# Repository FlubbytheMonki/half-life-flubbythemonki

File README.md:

I recently started working on starbie, a physical, sort of tomogotchi thats a star. It responds to your actions with controls on the board itself, designed in Kicad. 
This is really cool. Theres a menu that you can control with the buttons on the side and everything lays on the design that we made in Kicad. 
I feel like KiCad opened a whole new aspect of embedded programming that I never knew about. I thought pcbs were really hard to do but turns out that that isnt entirely the case.

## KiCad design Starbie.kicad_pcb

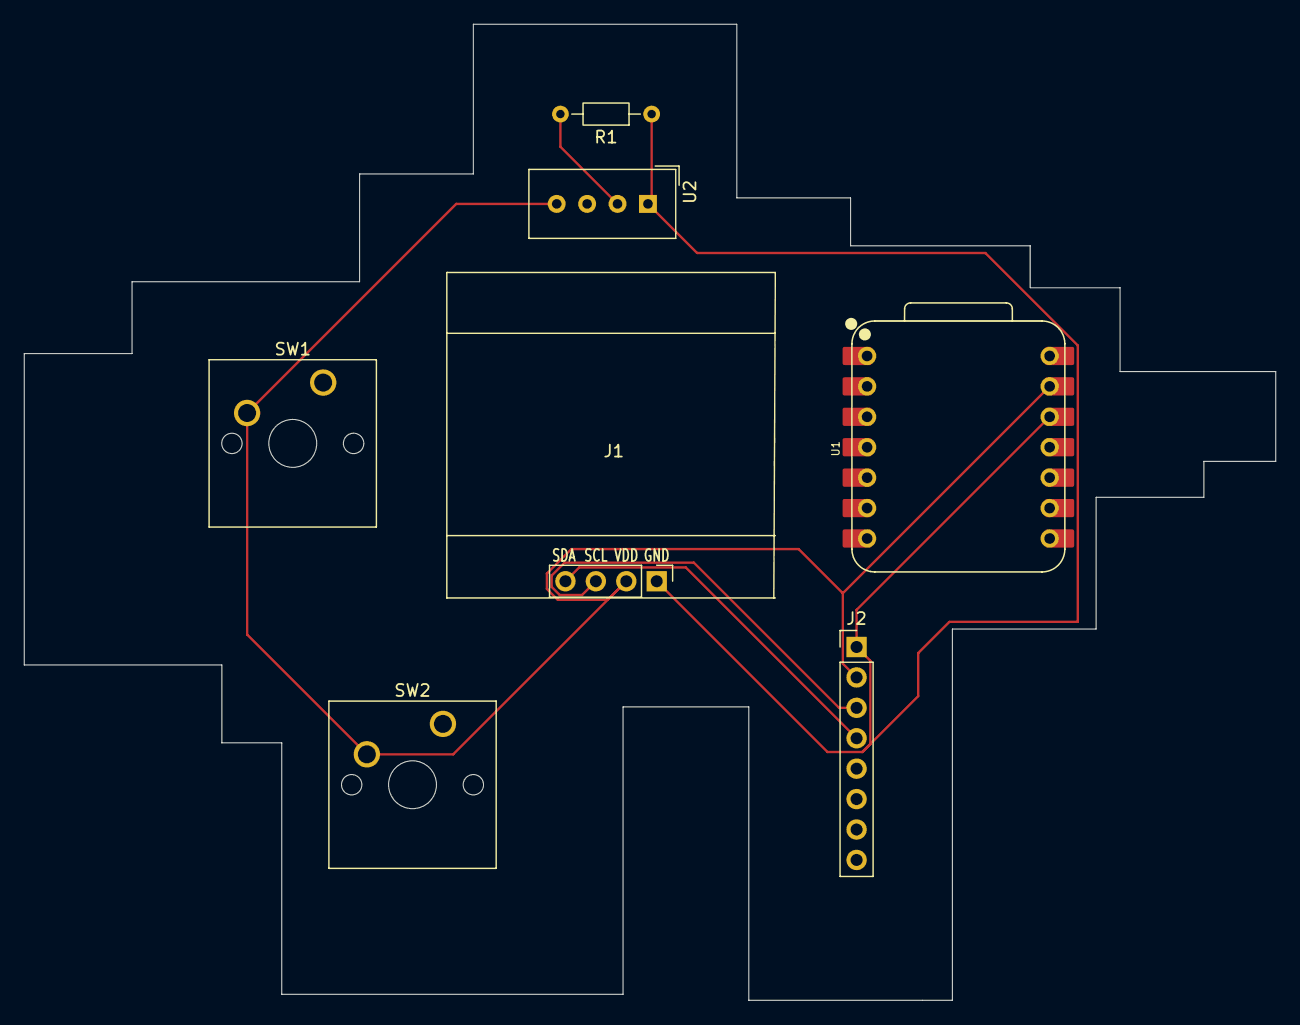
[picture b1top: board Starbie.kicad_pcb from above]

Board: 2 copper layers, 104.5 x 81.5 mm, 7 parts (0 on the bottom side), 5 nets.

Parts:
J1: Conn_01x04_Pin; Display_128x64_096_I2C
J2: Conn_01x08_Pin; PinHeader_1x08_P2.54mm_Vertical
R1: 10k; R_Axial_DIN0204_L3.6mm_D1.6mm_P7.62mm_Horizontal
SW1, SW2: SW_Push; SW_Cherry_MX_1.00u_PCB
U1: XIAO-ESP32-C3-SMD; XIAO-ESP32-C6-DIP
U2: DHT11; Aosong_DHT11_5.5x12.0_P2.54mm

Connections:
+3.3V: J1.1, J2.1, R1.1, U1.12 (3V3_OUT), U2.1 (VDD)
/DHT11 DATA: R1.2, U2.2 (DATA)
/SCL: J1.3, J2.3
/SDA: J1.4, J2.4
GND: J1.2, J2.2, SW1.2, SW2.2, U1.13 (GND), U2.4 (GND)
